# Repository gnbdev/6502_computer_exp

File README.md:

# 6502_computer_exp
6502 computer experiment with 6502 CPU and SRAM EEPROM VIA 6522 ACIA 6551

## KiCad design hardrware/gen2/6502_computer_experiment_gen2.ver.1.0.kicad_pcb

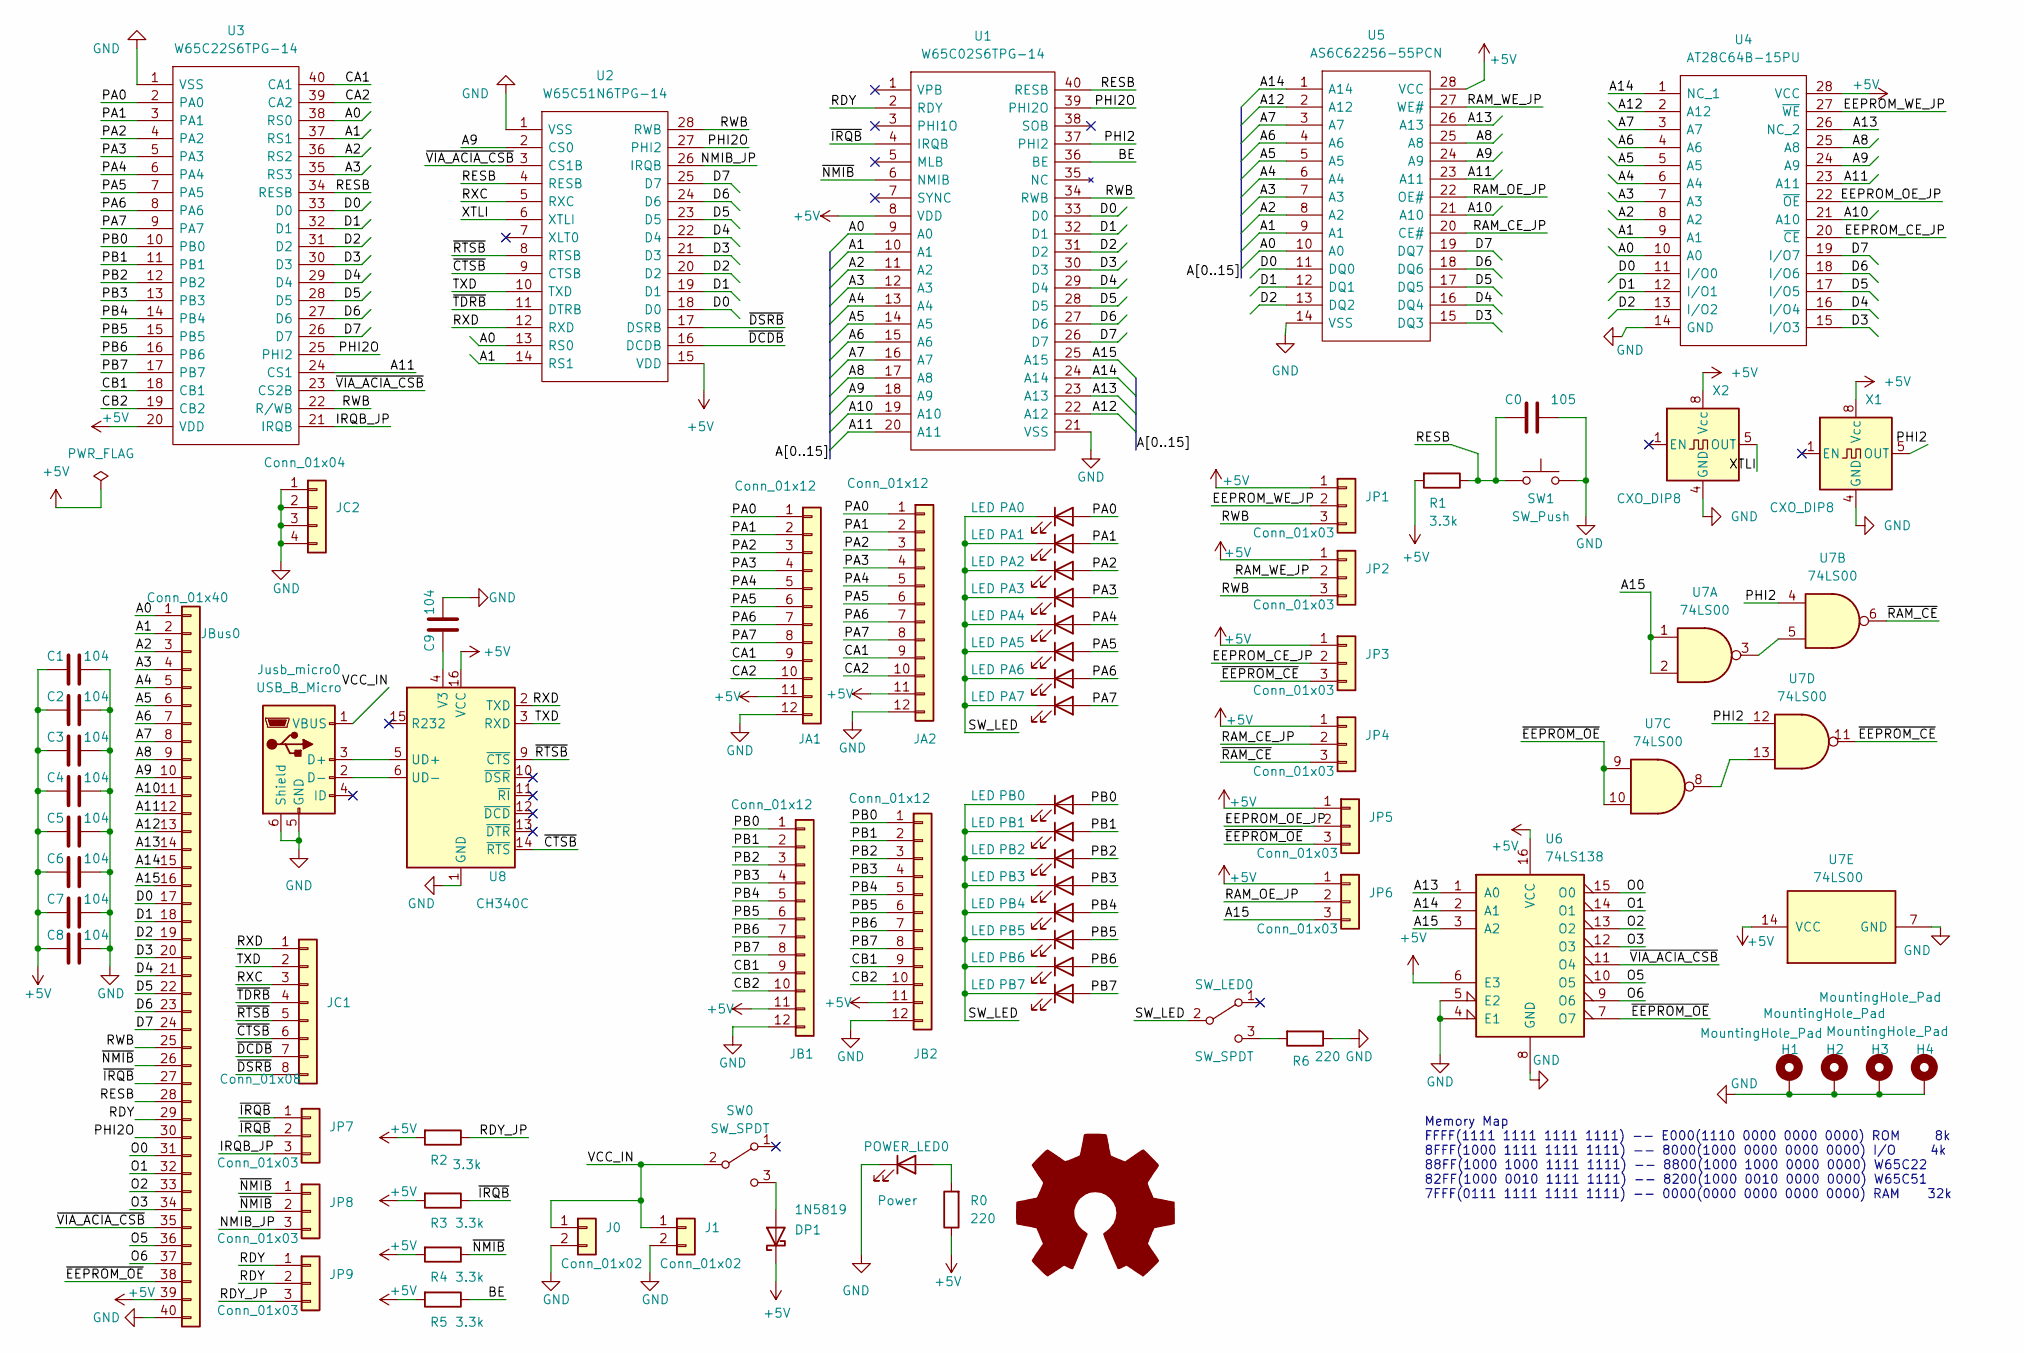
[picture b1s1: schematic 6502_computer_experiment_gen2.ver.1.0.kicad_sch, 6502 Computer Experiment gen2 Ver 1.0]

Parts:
C0: 105; C_Disc_D4.7mm_W2.5mm_P5.00mm
C1, C2, C3, C4, C5, C6, C7, C8, C9: 104; C_Disc_D4.7mm_W2.5mm_P5.00mm
DP1: 1N5819; D_DO-41_SOD81_P10.16mm_Horizontal
H1, H2, H3, H4: MountingHole_Pad; MountingHole_3.2mm_M3_Pad_Via
J0, J1: Conn_01x02; PinHeader_1x02_P2.54mm_Vertical
JA1, JA2: Conn_01x12; PinSocket_1x12_P2.54mm_Vertical
JB1, JB2: Conn_01x12; PinSocket_1x12_P2.54mm_Vertical
JBus0: Conn_01x40; PinHeader_1x40_P2.54mm_Vertical
JC1: Conn_01x08; PinHeader_1x08_P2.54mm_Vertical
JC2: Conn_01x04; PinHeader_1x04_P2.54mm_Vertical
JP1, JP2, JP3, JP4, JP5, JP6, JP7, JP8, JP9: Conn_01x03; PinHeader_1x03_P2.54mm_Vertical
Jusb_micro0: USB_B_Micro; USB_Micro-B_Molex-105017-0001
KiCadLOGO1: Logo_Open_Hardware_Large; KiCad-Logo2_5mm_SilkScreen
PA0, PA1, PA2, PA3, PA4, PA5, PA6, PA7: LED; LED_D3.0mm
PB0, PB1, PB2, PB3, PB4, PB5, PB6, PB7: LED; LED_D3.0mm
POWER_LED0: Power; LED_D3.0mm
R0, R6: 220; R_Axial_DIN0207_L6.3mm_D2.5mm_P10.16mm_Horizontal
R1, R2, R3, R4, R5: 3.3k; R_Axial_DIN0207_L6.3mm_D2.5mm_P10.16mm_Horizontal
SW0: SW_SPDT; PinHeader_1x03_P2.54mm_Vertical
SW1: SW_Push; SW_PUSH_6mm
SW_LED0: SW_SPDT; PinHeader_1x03_P2.54mm_Vertical
U1: W65C02S6TPG-14; 3M_Textool_240-1288-00-0602J_2x20_P2.54mm; Mouser Part Number 955-W65C02S6TPG-14
U2: W65C51N6TPG-14; DIP_Socket-28_W11.9_W12.7_W15.24_W17.78_W18.5_3M_228-1277-0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; Mouser Part Number 955-W65C51N6TPG-14
U3: W65C22S6TPG-14; 3M_Textool_240-1288-00-0602J_2x20_P2.54mm; Mouser Part Number 955-W65C22S6TPG-14
U4: AT28C64B-15PU; DIP_Socket-28_W11.9_W12.7_W15.24_W17.78_W18.5_3M_228-1277-0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; Mouser Part Number 556-AT28C64B15PU
U5: AS6C62256-55PCN; DIP_Socket-28_W11.9_W12.7_W15.24_W17.78_W18.5_3M_228-1277-0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; Mouser Part Number 913-AS6C62256-55PCN
U6: 74LS138; DIP-16_W7.62mm_Socket
U7: 74LS00; DIP-14_W7.62mm_Socket
U8: CH340C; SOIC-16_3.9x9.9mm_P1.27mm
X1, X2: CXO_DIP8; Oscillator_DIP-8

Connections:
+5V: C1.1, C2.1, C3.1, C4.1, C5.1, C6.1, C7.1, C8.1, DP1.1 (K), JA1.11, JA2.11, JB1.11, JB2.11, JBus0.39, JP1.1, JP2.1, JP3.1, JP4.1, JP5.1, JP6.1, R0.1, R1.2, R2.2, R3.2, R4.2, R5.2, U1.8 (VDD), U2.15 (VDD), U3.20 (VDD), U4.28 (VCC), U5.28 (VCC), U6.6 (E3), U6.16 (VCC), U7.14 (VCC), U8.16 (VCC), X1.8 (Vcc), X2.8 (Vcc)
/A0: JBus0.1, U1.9 (A0), U2.13 (RS0), U3.38 (RS0), U4.10 (A0), U5.10 (A0)
/A1: JBus0.2, U1.10 (A1), U2.14 (RS1), U3.37 (RS1), U4.9 (A1), U5.9 (A1)
/A2: JBus0.3, U1.11 (A2), U3.36 (RS2), U4.8 (A2), U5.8 (A2)
/A3: JBus0.4, U1.12 (A3), U3.35 (RS3), U4.7 (A3), U5.7 (A3)
/A4: JBus0.5, U1.13 (A4), U4.6 (A4), U5.6 (A4)
/A5: JBus0.6, U1.14 (A5), U4.5 (A5), U5.5 (A5)
/A6: JBus0.7, U1.15 (A6), U4.4 (A6), U5.4 (A6)
/A7: JBus0.8, U1.16 (A7), U4.3 (A7), U5.3 (A7)
/A8: JBus0.9, U1.17 (A8), U4.25 (A8), U5.25 (A8)
/A9: JBus0.10, U1.18 (A9), U2.2 (CS0), U4.24 (A9), U5.24 (A9)
/A10: JBus0.11, U1.19 (A10), U4.21 (A10), U5.21 (A10)
/A11: JBus0.12, U1.20 (A11), U3.24 (CS1), U4.23 (A11), U5.23 (A11)
/A12: JBus0.13, U1.22 (A12), U4.2 (A12), U5.2 (A12)
/A13: JBus0.14, U1.23 (A13), U4.26 (NC_2), U5.26 (A13), U6.1 (A0)
/A14: JBus0.15, U1.24 (A14), U4.1 (NC_1), U5.1 (A14), U6.2 (A1)
/A15: JBus0.16, JP6.3, U1.25 (A15), U6.3 (A2), U7.1, U7.2
/BE: R5.1, U1.36 (BE)
/CA1: JA1.9, JA2.9, U3.40 (CA1)
/CA2: JA1.10, JA2.10, U3.39 (CA2)
/CB1: JB1.9, JB2.9, U3.18 (CB1)
/CB2: JB1.10, JB2.10, U3.19 (CB2)
/D0: JBus0.17, U1.33 (D0), U2.18 (D0), U3.33 (D0), U4.11 (I/O0), U5.11 (DQ0)
/D1: JBus0.18, U1.32 (D1), U2.19 (D1), U3.32 (D1), U4.12 (I/O1), U5.12 (DQ1)
/D2: JBus0.19, U1.31 (D2), U2.20 (D2), U3.31 (D2), U4.13 (I/O2), U5.13 (DQ2)
/D3: JBus0.20, U1.30 (D3), U2.21 (D3), U3.30 (D3), U4.15 (I/O3), U5.15 (DQ3)
/D4: JBus0.21, U1.29 (D4), U2.22 (D4), U3.29 (D4), U4.16 (I/O4), U5.16 (DQ4)
/D5: JBus0.22, U1.28 (D5), U2.23 (D5), U3.28 (D5), U4.17 (I/O5), U5.17 (DQ5)
/D6: JBus0.23, U1.27 (D6), U2.24 (D6), U3.27 (D6), U4.18 (I/O6), U5.18 (DQ6)
/D7: JBus0.24, U1.26 (D7), U2.25 (D7), U3.26 (D7), U4.19 (I/O7), U5.19 (DQ7)
/EEPROM_CE_JP: JP3.2, U4.20 (~CE)
/EEPROM_OE_JP: JP5.2, U4.22 (~OE)
/EEPROM_WE_JP: JP1.2, U4.27 (~WE)
/IRQB_JP: JP7.3, U3.21 (IRQB)
/NMIB_JP: JP8.3, U2.26 (IRQB)
/O0: JBus0.31, U6.15 (O0)
/O1: JBus0.32, U6.14 (O1)
/O2: JBus0.33, U6.13 (O2)
/O3: JBus0.34, U6.12 (O3)
/O5: JBus0.36, U6.10 (O5)
/O6: JBus0.37, U6.9 (O6)
/PA0: JA1.1, JA2.1, PA0.2 (A), U3.2 (PA0)
/PA1: JA1.2, JA2.2, PA1.2 (A), U3.3 (PA1)
/PA2: JA1.3, JA2.3, PA2.2 (A), U3.4 (PA2)
/PA3: JA1.4, JA2.4, PA3.2 (A), U3.5 (PA3)
/PA4: JA1.5, JA2.5, PA4.2 (A), U3.6 (PA4)
/PA5: JA1.6, JA2.6, PA5.2 (A), U3.7 (PA5)
/PA6: JA1.7, JA2.7, PA6.2 (A), U3.8 (PA6)
/PA7: JA1.8, JA2.8, PA7.2 (A), U3.9 (PA7)
/PB0: JB1.1, JB2.1, PB0.2 (A), U3.10 (PB0)
/PB1: JB1.2, JB2.2, PB1.2 (A), U3.11 (PB1)
/PB2: JB1.3, JB2.3, PB2.2 (A), U3.12 (PB2)
/PB3: JB1.4, JB2.4, PB3.2 (A), U3.13 (PB3)
/PB4: JB1.5, JB2.5, PB4.2 (A), U3.14 (PB4)
/PB5: JB1.6, JB2.6, PB5.2 (A), U3.15 (PB5)
/PB6: JB1.7, JB2.7, PB6.2 (A), U3.16 (PB6)
/PB7: JB1.8, JB2.8, PB7.2 (A), U3.17 (PB7)
/PHI2: U1.37 (PHI2), U7.4, U7.12, X1.5 (OUT)
/PHI2O: JBus0.30, U1.39 (PHI2O), U2.27 (PHI2), U3.25 (PHI2)
/RAM_CE_JP: JP4.2, U5.20 (CE#)
/RAM_OE_JP: JP6.2, U5.22 (OE#)
/RAM_WE_JP: JP2.2, U5.27 (WE#)
/RDY: JBus0.29, JP9.1, JP9.2, U1.2 (RDY)
/RDY_JP: JP9.3, R2.1
/RESB: C0.1, JBus0.28, R1.1, SW1.1, U1.40 (RESB), U2.4 (RESB), U3.34 (RESB)
/RWB: JBus0.25, JP1.3, JP2.3, U1.34 (RWB), U2.28 (RWB), U3.22 (R/WB)
/RXC: JC1.3, U2.5 (RXC)
/RXD: JC1.1, U2.12 (RXD), U8.2 (TXD)
/SW_LED: PA0.1 (K), PA1.1 (K), PA2.1 (K), PA3.1 (K), PA4.1 (K), PA5.1 (K), PA6.1 (K), PA7.1 (K), PB0.1 (K), PB1.1 (K), PB2.1 (K), PB3.1 (K), PB4.1 (K), PB5.1 (K), PB6.1 (K), PB7.1 (K), SW_LED0.2 (B)
/TXD: JC1.2, U2.10 (TXD), U8.3 (RXD)
/VCC_IN: J0.1, J1.1, Jusb_micro0.1 (VBUS), SW0.2 (B)
/XTLI: U2.6 (XTLI), X2.5 (OUT)
/~CTSB: JC1.6, U2.9 (CTSB), U8.14 (~RTS)
/~DCDB: JC1.7, U2.16 (DCDB)
/~DSRB: JC1.8, U2.17 (DSRB)
/~EEPROM_CE: JP3.3, U7.11
/~EEPROM_OE: JBus0.38, JP5.3, U6.7 (O7), U7.9, U7.10
/~IRQB: JBus0.27, JP7.1, JP7.2, R3.1, U1.4 (IRQB)
/~NMIB: JBus0.26, JP8.1, JP8.2, R4.1, U1.6 (NMIB)
/~RAM_CE: JP4.3, U7.6
/~RTSB: JC1.5, U2.8 (RTSB), U8.9 (~CTS)
/~TDRB: JC1.4, U2.11 (DTRB)
/~VIA_ACIA_CSB: JBus0.35, U2.3 (CS1B), U3.23 (CS2B), U6.11 (O4)
GND: C0.2, C1.2, C2.2, C3.2, C4.2, C5.2, C6.2, C7.2, C8.2, C9.2, H1.1, H2.1, H3.1, H4.1, J0.2, J1.2, JA1.12, JA2.12, JB1.12, JB2.12, JBus0.40, JC2.1, JC2.2, JC2.3, JC2.4, Jusb_micro0.5 (GND), Jusb_micro0.6 (Shield), POWER_LED0.1 (K), R6.1, SW1.2, U1.21 (VSS), U2.1 (VSS), U3.1 (VSS), U4.14 (GND), U5.14 (VSS), U6.4 (E1), U6.5 (E2), U6.8 (GND), U7.7 (GND), U8.1 (GND), X1.4 (GND), X2.4 (GND)
unnamed: C9.1, U8.4 (V3)
unnamed: DP1.2 (A), SW0.3 (C)
unnamed: Jusb_micro0.2 (D-), U8.6 (UD-)
unnamed: Jusb_micro0.3 (D+), U8.5 (UD+)
unnamed: POWER_LED0.2 (A), R0.2
unnamed: R6.2, SW_LED0.3 (C)
unnamed: U7.3, U7.5
unnamed: U7.8, U7.13

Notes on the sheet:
Memory Map FFFF(1111 1111 1111 1111) -- E000(1110 0000 0000 0000) ROM 8k 8FFF(1000 1111 1111 1111) -- 8000(1000 0000 0000 0000) I/O 4k 88FF(1000 1000 1111 1111) -- 8800(1000 1000 0000 0000) W65C22 82FF(1000 0010 1111 1111) -- 8200(1000 0010 0000 0000) W65C51 7FFF(0111 1111 1111 1111) -- 0000(0000 0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

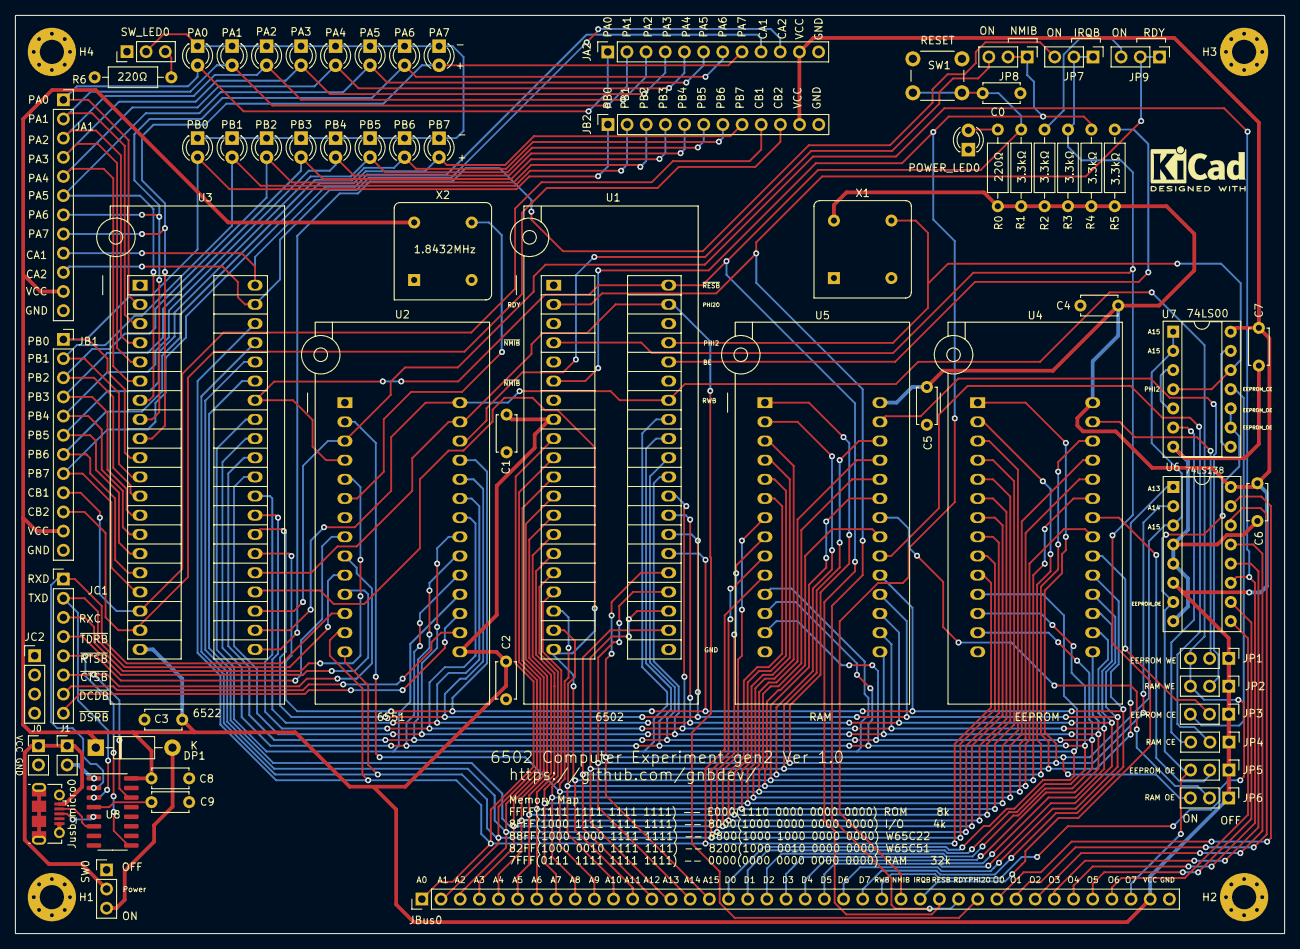
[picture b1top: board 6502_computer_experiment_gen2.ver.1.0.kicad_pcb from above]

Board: 2 copper layers, 168.2 x 121.7 mm, 72 parts (0 on the bottom side), 92 nets.

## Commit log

2023-04-06 gen 1
2023-04-28 gen2
2023-05-16 add software
